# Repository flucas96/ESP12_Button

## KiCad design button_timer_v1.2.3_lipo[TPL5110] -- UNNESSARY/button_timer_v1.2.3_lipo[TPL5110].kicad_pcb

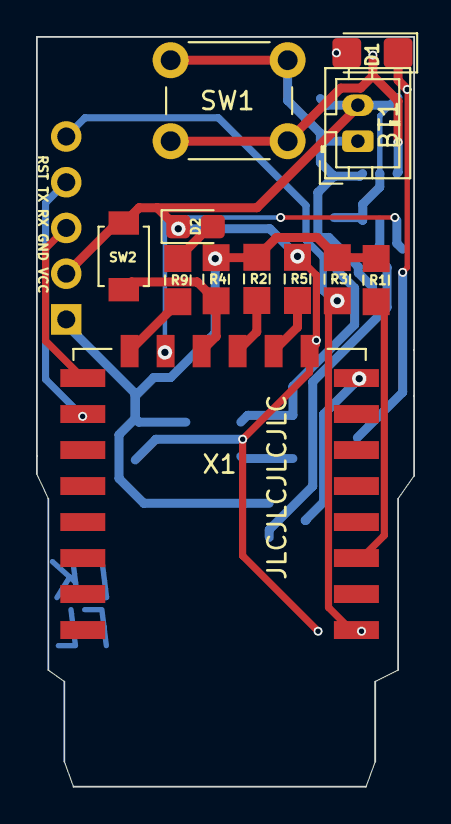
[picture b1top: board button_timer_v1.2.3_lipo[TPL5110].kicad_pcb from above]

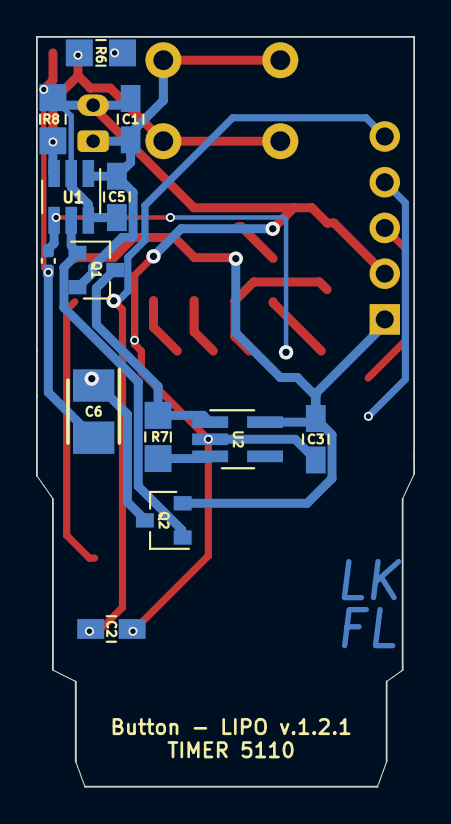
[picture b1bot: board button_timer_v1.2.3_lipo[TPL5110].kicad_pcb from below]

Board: 2 copper layers, 21.0 x 41.7 mm, 26 parts (13 on the bottom side), 19 nets.

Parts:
BT1: Battery_Cell; JST_PH_B2B-PH-K_1x02_P2.00mm_Vertical
C1, C3: 10uF; C_0805_2012handsodermod
C2, C5: 100nF; C_0805_2012handsodermod
C4: 10nf-100nf; C_0402_1005Metric_Pad0.74x0.62mm_HandSolder
C6: TAJB476M010TNJ; CAPPM3528X210N
D1: LED; LED_1206_3216Metric_Castellated
D2: LED; LED_0805_2012Metric_Castellated_mod
J1: Conn_01x05_Female; PinSocket_1x05_P2.54mm_Vertical_mod
Q1, Q2: TSM2301ACX; SOT-23
R1, R2, R3, R4, R8: 10k; R_0805_2012handsoldermod
R5: 4.7k; R_0805_2012handsoldermod
R6, R9: 1k; R_0805_2012handsoldermod
R7: 100k; R_0805_2012handsoldermod
SW1: SW_Push; SW_PUSH_6mm_H8mm_mod
SW2: SW_Push; SW_SPST_B3U-1000P_mod
U1: TPL5110; SOT-23-6handsoldering
U2: AP2112K-3.3; SOT-23-5_HandSolderingmod
X1: ESP-12E; ESP-12Elesssilk

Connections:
/EN: R1.2, X1.3
/GND: BT1.2, C1.1, C2.1, C3.1, C4.2, C5.1, C6.2, D1.1, D2.1, J1.2, R5.1, R8.2, SW2.2, U1.2, U1.6, U2.2, X1.9
/GPIO0: R4.2, SW2.1, X1.12
/GPIO2: R2.2, X1.11
/GPIO4: C4.1, U1.4, X1.13
/GPIO5: R9.2, X1.14
/GPIO15: R5.2, X1.10
/RST: C2.2, J1.5, R3.2, X1.1
/RX: J1.3, X1.15
/TX: J1.4, X1.16
/VCC: C3.2, J1.1, Q2.2, R1.1, R2.1, R3.1, R4.1, U2.5
/VCC_ESP: C6.1, Q2.3, X1.8
unnamed: BT1.1, C1.2, C5.2, Q1.2, SW1.1, U1.1
unnamed: D1.2, R6.1
unnamed: D2.2, R9.1
unnamed: Q1.1, Q2.1, U1.5
unnamed: Q1.3, R7.1, U2.1
unnamed: R6.2, R8.1, SW1.2, U1.3
unnamed: R7.2, U2.3

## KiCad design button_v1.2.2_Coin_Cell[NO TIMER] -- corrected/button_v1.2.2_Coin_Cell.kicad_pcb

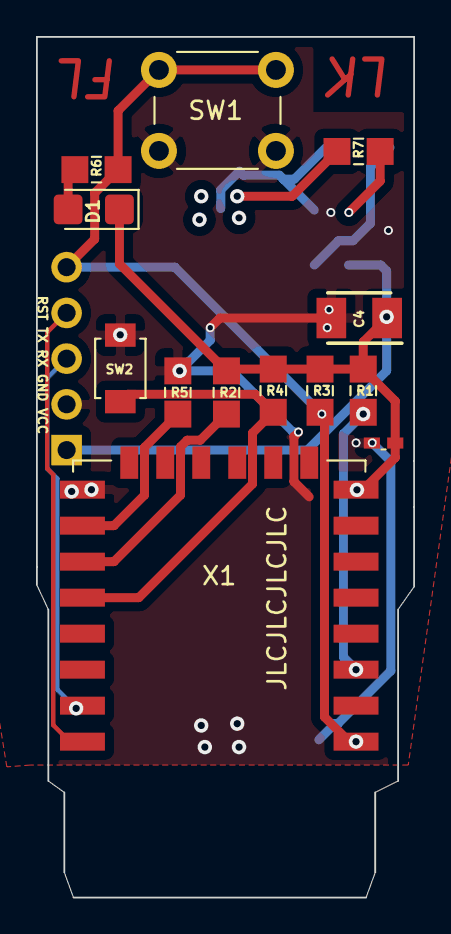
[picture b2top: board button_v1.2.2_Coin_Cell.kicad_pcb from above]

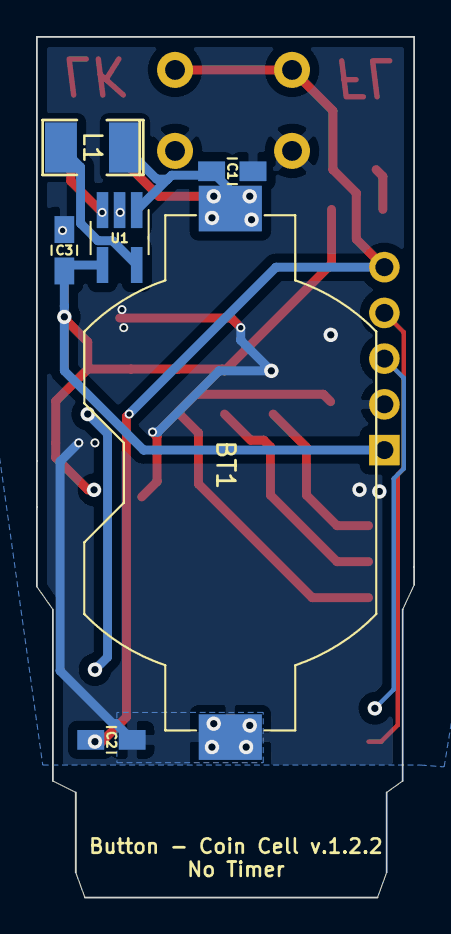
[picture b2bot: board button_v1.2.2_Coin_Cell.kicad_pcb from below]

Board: 2 copper layers, 21.0 x 47.8 mm, 20 parts (6 on the bottom side), 13 nets.

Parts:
BT1: Battery_Cell; BatteryHolder_Keystone_1058_1x2032
C1, C3: 10uF; C_0805_2012handsodermod
C2: 100nF; C_0805_2012handsodermod
C4: TAJB476M010TNJ; CAPPM3528X210N
C5: 100nF; C_0402_1005Metric_Pad0.74x0.62mm_HandSoldermod
D1: LED; LED_1206_3216Metric_Castellated
J1: Conn_01x05_Female; PinSocket_1x05_P2.54mm_Vertical_mod
L1: 4.7 uH; SMD-1210_Pol_inductor
R1, R2, R3, R4: 10k; R_0805_2012handsoldermod
R5: 4.7k; R_0805_2012handsoldermod
R6: 1k; R_0805_2012handsoldermod
R7: 100k; R_0805_2012handsoldermod
SW1: SW_Push; SW_PUSH_6mm_H8mm_mod
SW2: SW_Push; SW_SPST_B3U-1000P_mod
U1: TPS61097A; SOT-23-5_HandSolderingmod
X1: ESP-12E; ESP-12Elesssilk

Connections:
/EN: R1.2, X1.3
/GND: BT1.2, C1.1, C2.1, C3.2, C4.2, C5.2, J1.2, R5.1, SW1.2, SW2.2, U1.2, X1.15
/GPIO0: R4.2, SW2.1, X1.18
/GPIO2: R2.2, X1.17
/GPIO15: R5.2, X1.16
/RST: C2.2, J1.5, R3.2, R6.2, SW1.1, X1.1
/RX: J1.3, X1.21
/TX: J1.4, X1.22
/VCC: C3.1, C4.1, C5.1, D1.1, J1.1, R1.1, R2.1, R3.1, R4.1, U1.4, X1.8
unnamed: BT1.1, C1.2, L1.1, R7.1, U1.1
unnamed: D1.2, R6.1
unnamed: L1.2, U1.5
unnamed: R7.2, U1.3
